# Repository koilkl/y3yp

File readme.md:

# 🥾 Next-Generation Ankle Rehabilitation System (Actuation Belt Trainer)

Welcome to the official repository for the **Next-Generation Ankle Rehabilitation System**, a biomechanically engineered solution designed to build structural resilience and prevent trail-induced lower-limb injuries. 

## 👥 Meet the Team
**Hikingggggggg(HKUST 2026 ISDN3001&ISDN3002 Group 1)**
* Teammate:Kwok Tsz Yueng
  * Kwok Tsz Yueng(Tom)
  * Li,Kaile(Koil)
  * Lee Wang Ngai(Cyrus)
  * Yu Kin Shing(Ken)

We are a team of passionate engineers and biomechanics enthusiasts dedicated to bridging the gap between clinical rehabilitation and real-world outdoor sports readiness.

---

## 🏔️ Project Overview

### The Problem: The Hiking Injury Epidemic
With the massive global expansion of hiking participation, there has been a severe spike in trail-induced injuries. 
* **Acute Lateral Sprains** account for an overwhelming 85% of all acute trail traumas.
* In competitive downhill races, lower-limb injury rates spike dramatically to 49%.
* Hikers face a **"Deficit in Terrain Adaptability"**; modern flat surfaces fail to prepare the body for the eccentric braking and instantaneous balance reflexes required on unpredictable mountain terrains (like loose rock and scree).

When a sudden, forceful ankle inversion exceeds 25 degrees, it tears the Anterior Talofibular and Calcaneofibular ligaments. 

### The Solution: The Actuation Belt Trainer
Existing market solutions force a compromise: balance boards train reflexes but lack heavy external load, while clinical dynamometers are expensive and lack multi-axis functional movement. 

After multiple ideation phases (including dynamic treadmills and linear pedal trainers), we finalized the **Actuation Belt Trainer**. This active, stationary device isolates the protective reflex arc by applying changeable, programmable external loads to train specific muscle reaction times across 3 Degrees of Freedom (DOFs).

---

## ⚙️ System Architecture

Our system integrates responsive hardware with a closed-loop software control mechanism to ensure precise resistance and user safety.

### Control Loop Workflow
1. **Command Input:** Users input commands via a terminal to wirelessly control motor force and turning direction for specific muscle targeting.
2. **Processing & Communication:** A Microcontroller Unit (MCU) processes the command using a PID controller and sends signals via a CAN Module to 6 Motor Electronic Speed Controllers (ESCs).
3. **IMU Feedback:** An Inertial Measurement Unit (IMU) under the pedal continuously detects the XYZ angle of the pedal.
4. **Evaluation & Visual Feedback:** The MCU calculates the control error against the target origin angle. If the user successfully holds the pedal within a +/- 10-degree range against the motor resistance for 5 seconds, an LED indicator triggers to signal successful completion.

---

## 🛠️ Component Design

The mechanical structure relies on motor-driven belts and gears to safely and effectively stimulate the ankle:

* **Roll Mechanism (Inversion/Eversion):** Four M3508 motors utilize a 1:1 gear transmission to transfer torque to a pulley system. This produces tension along an elastic belt connected to the pedal, creating a twisting motion that the user must resist.
* **Pitch Mechanism (Dorsiflexion/Plantarflexion):** A motor and gear turn the entire middle module and the central pedal, supported by a large external bearing for smooth turning. A limited angle of gear teeth physically restricts motion to guarantee it remains within an acceptable, safe anatomical range.

---

## 🔬 Biomechanical Validation

The system targets the biological failure points of the ankle by isolating the primary protective muscles:
* **Fibularis (Peroneal) Group:** Primary evertors critical for resisting sudden inward ankle rolling (inversion) on shifting scree.
* **Tibialis Group:** Crucial for dorsiflexion, arch support, and absorbing repeated impact with controlled eccentric braking during steep descents.

By engineering a device that challenges the ankle with resisted eversion and perturbation, the system is theoretically proven to improve strength and balance deficits.

---

## 🚀 Future Roadmap

* **Weeks 1-3:** Develop a dedicated mobile app for user control, design a "hiking-like" training mode, and improve mechanism functionalities.
* **Weeks 4-6:** Design pedals to fit different foot sizes, replace electronics to minimize overall device size, and refine the product outfit.
* **Weeks 6-7:** Conduct extensive user testing, identify potential new user groups, and perform evaluations based on feedback.
* **Weeks 7-8:** Design new features and establish a future plan for product line depth to fit various target demographics.

---

## 💾 Cloning This Repository

The repo uses **git submodules** (firmware) and **Git LFS** (large media files):

```bash
# 1. Install Git LFS (once per machine)
#    macOS:      brew install git-lfs
#    Windows:    winget install Git.LFS
#    Ubuntu:     sudo apt install git-lfs
git lfs install

# 2. Clone with submodules
git clone --recursive https://github.com/koilkl/y3yp.git
```

* `git lfs install` sets up the LFS filters on your machine. Without it, LFS-tracked files (e.g. `*.mp4`) are checked out as small pointer files instead of the real content.
* Already cloned without LFS support? Run `git lfs install && git lfs pull` to download the tracked files.
* `--recursive` fetches the firmware submodules under `ELEC/`; alternatively run `git submodule update --init --recursive` inside an existing clone.

## 📂 Repository Structure

```
y3yp/
├── DOCUMENT/                 # Presentations & demo video
│   └── Version-1.0/
│       ├── Midterm Presentation.pptx
│       ├── Final Presentation.pdf
│       └── demo video.mp4
├── ELEC/                     # Electronics & firmware
│   ├── Version-1.0/
│   │   └── Year_3_first_prototype/   # submodule: STM32F103C6T6, CAN motors + IMU + PID
│   └── Component/
│       └── Incliometer/              # submodule: STM32F401RETx, Modbus-RTU inclinometer
├── MECH/                     # Mechanical design (CAD)
│   └── Version-1.0/
│       └── Gen1-belt.zip             # Belt-actuation assembly (STEP)
└── readme.md                 # This file
```

## 📁 Resources & Appendices

* **CAD Files & 3D Renders:** [`MECH/Version-1.0/Gen1-belt.zip`](MECH/Version-1.0/Gen1-belt.zip)
* **Source Code (First Prototype):** [`yuu033/Year_3_first_prototype`](https://github.com/yuu033/Year_3_first_prototype) (submodule at [`ELEC/Version-1.0/Year_3_first_prototype/`](ELEC/Version-1.0/))
* **Source Code (Inclinometer Component):** [`koilkl/Incliometer`](https://github.com/koilkl/Incliometer) (submodule at [`ELEC/Component/Incliometer/`](ELEC/Component/))
* **Presentations:** [`DOCUMENT/Version-1.0/`](DOCUMENT/Version-1.0/README.md)
* **Prototype Demo Video:** [`DOCUMENT/Version-1.0/demo video.mp4`](DOCUMENT/Version-1.0/demo%20video.mp4)

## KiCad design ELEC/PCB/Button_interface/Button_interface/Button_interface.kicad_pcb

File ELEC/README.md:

# ⚡ ELEC — Electronics & Firmware

All electronics and embedded firmware for the **Actuation Belt Trainer**.

> The two firmware projects are **git submodules** pointing at their own repositories. Clone this repo with:
> ```bash
> git clone --recursive https://github.com/koilkl/y3yp.git
> ```
> If you already cloned without `--recursive`, run `git submodule update --init --recursive`.

## Layout

| Path | Description |
|------|-------------|
| [`Version-1.0/Year_3_first_prototype`](https://github.com/yuu033/Year_3_first_prototype) | Full first-prototype firmware (STM32F103C6T6): CAN motor control (C620 ESCs), IMU feedback (BMI270 + Modbus IMU), PID control loop |
| [`Component/Incliometer`](https://github.com/koilkl/Incliometer) | Standalone inclinometer data-acquisition project (STM32F401RETx, Modbus-RTU) used to validate pedal angle sensing |

## System Context

Both projects are STM32CubeMX-generated HAL projects built with CMake (`arm-none-eabi` GCC + Ninja). Together they implement the control loop described in the main [README](../readme.md): the MCU reads the pedal angle from an IMU, runs a PID controller, and drives the M3508/C620 motors over CAN to apply programmable resistance.

## Related

- Mechanical design: [`../MECH/`](../MECH/README.md)
- Presentations & demo: [`../DOCUMENT/`](../DOCUMENT/README.md)

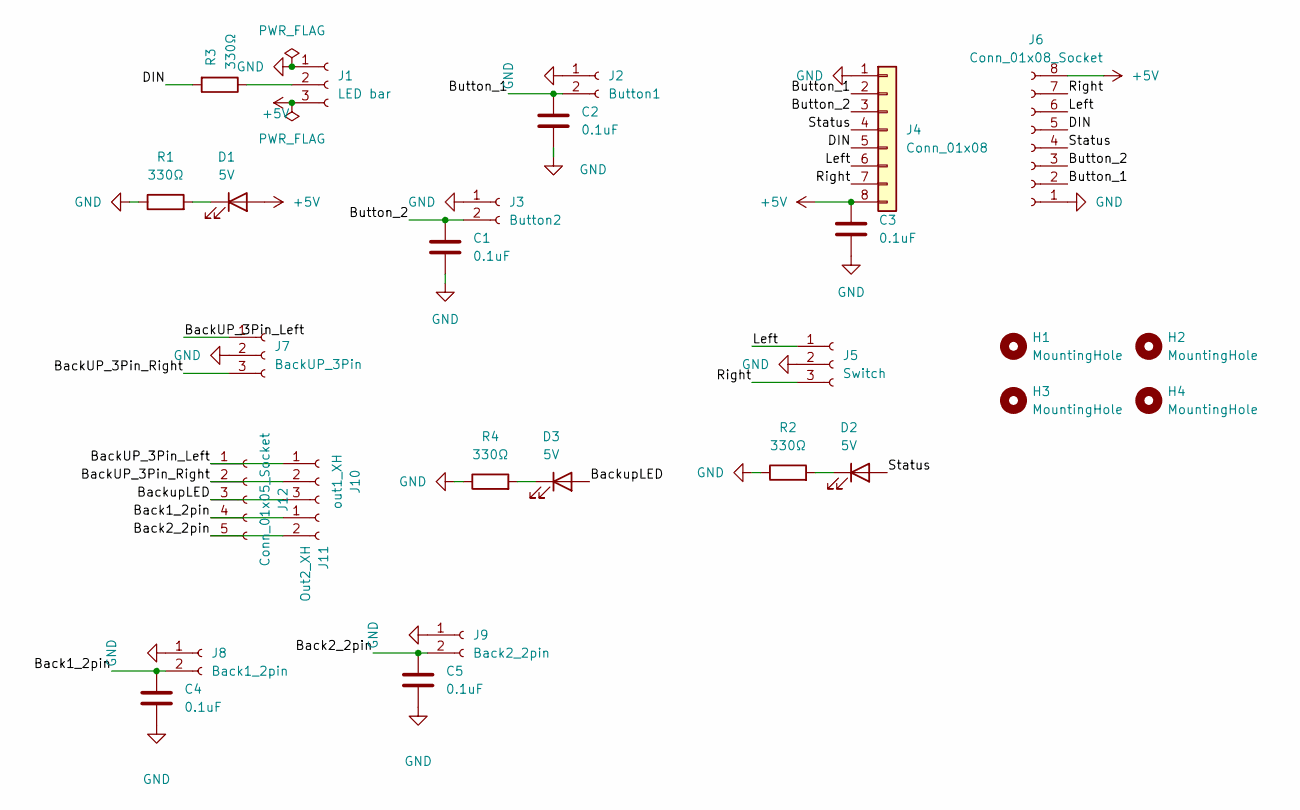
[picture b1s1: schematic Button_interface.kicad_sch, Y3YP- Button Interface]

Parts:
C1, C2, C3, C4, C5: 0.1uF; C_0805_2012Metric
D1, D2, D3: 5V; LED_D5.0mm
H1, H2, H3, H4: MountingHole; MountingHole_4.3mm_M4_DIN965_Pad
J1: LED bar; JST_XH_B3B-XH-A_1x03_P2.50mm_Vertical
J2: Button1; JST_XH_B2B-XH-A_1x02_P2.50mm_Vertical
J3: Button2; JST_XH_B2B-XH-A_1x02_P2.50mm_Vertical
J4: Conn_01x08; JST_XH_B8B-XH-A_1x08_P2.50mm_Vertical
J5: Switch; JST_XH_B3B-XH-A_1x03_P2.50mm_Vertical
J6: Conn_01x08_Socket; PinSocket_1x08_P2.54mm_Vertical
J7: BackUP_3Pin; JST_XH_B3B-XH-A_1x03_P2.50mm_Vertical
J8: Back1_2pin; JST_XH_B2B-XH-A_1x02_P2.50mm_Vertical
J9: Back2_2pin; JST_XH_B2B-XH-A_1x02_P2.50mm_Vertical
J10: out1_XH; JST_XH_B3B-XH-A_1x03_P2.50mm_Vertical
J11: Out2_XH; JST_XH_B2B-XH-A_1x02_P2.50mm_Vertical
J12: Conn_01x05_Socket; PinSocket_1x05_P2.54mm_Vertical
R1, R2, R3, R4: 330Ω; R_0805_2012Metric

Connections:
+5V: C3.1, D1.2 (A), J1.3, J4.8, J6.8
/Back1_2pin: C4.1, J8.2, J11.1, J12.4
/Back2_2pin: C5.1, J9.2, J11.2, J12.5
/BackUP_3Pin_Left: J7.1, J10.1, J12.1
/BackUP_3Pin_Right: J7.3, J10.2, J12.2
/BackupLED: D3.2 (A), J10.3, J12.3
/Button_1: C2.1, J2.2, J4.2, J6.2
/Button_2: C1.1, J3.2, J4.3, J6.3
/DIN: J4.5, J6.5, R3.2
/Left: J4.6, J5.1, J6.6
/Right: J4.7, J5.3, J6.7
/Status: D2.2 (A), J4.4, J6.4
GND: C1.2, C2.2, C3.2, C4.2, C5.2, J1.1, J2.1, J3.1, J4.1, J5.2, J6.1, J7.2, J8.1, J9.1, R1.1, R2.1, R4.1
unnamed: D1.1 (K), R1.2
unnamed: D2.1 (K), R2.2
unnamed: D3.1 (K), R4.2
unnamed: J1.2, R3.1

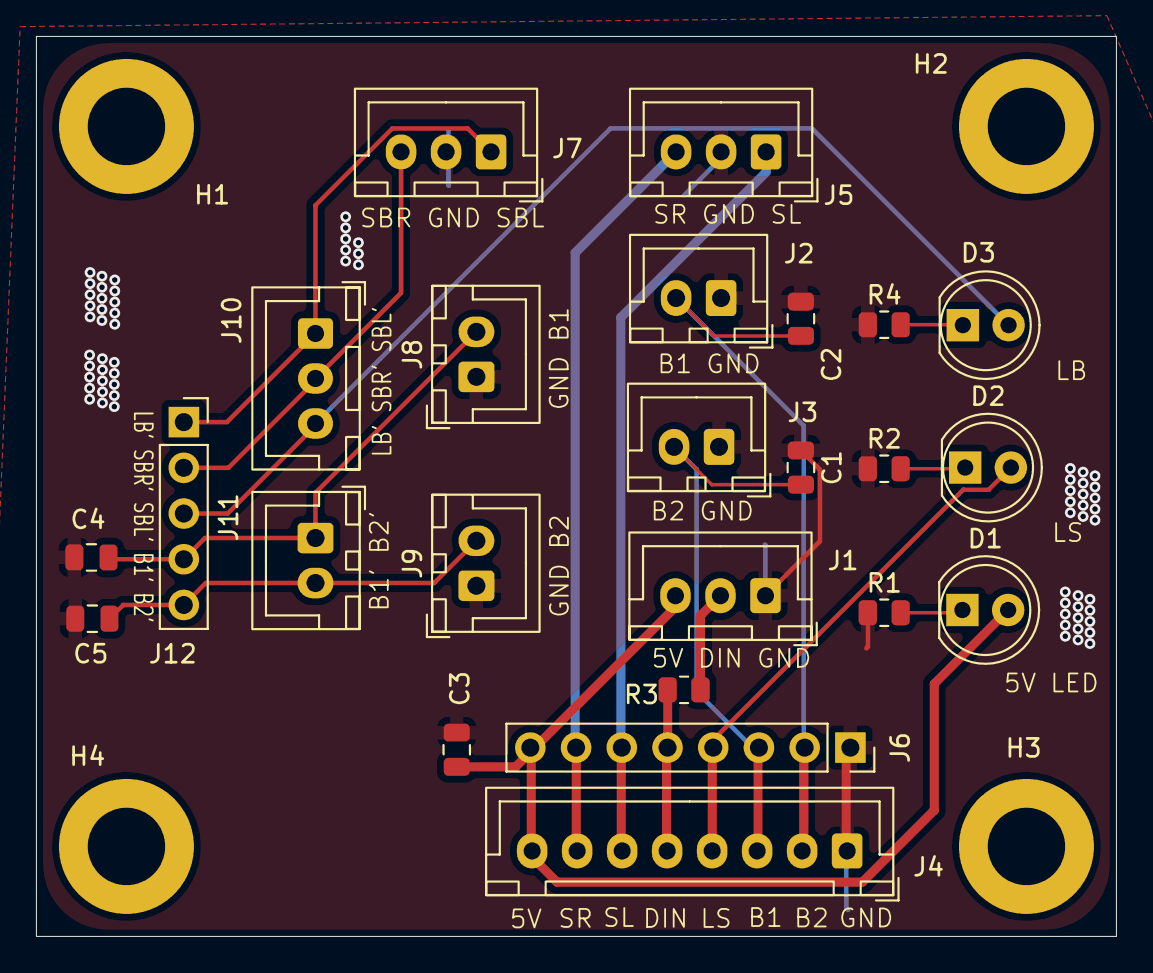
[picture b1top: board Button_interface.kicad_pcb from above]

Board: 2 copper layers, 60.0 x 50.0 mm, 28 parts (0 on the bottom side), 17 nets.

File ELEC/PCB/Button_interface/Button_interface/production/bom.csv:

Designator,Footprint,Quantity,Value,LCSC Part #
"C1, C2, C3, C4, C5",0805,5,0.1uF,
"D1, D2, D3",LED_D5.0mm,3,5V,
J1,JST_XH_B3B-XH-A_1x03_P2.50mm_Vertical,1,LED bar,
J10,JST_XH_B3B-XH-A_1x03_P2.50mm_Vertical,1,out1_XH,
J11,JST_XH_B2B-XH-A_1x02_P2.50mm_Vertical,1,Out2_XH,
J12,PinSocket_1x05_P2.54mm_Vertical,1,Conn_01x05_Socket,
J2,JST_XH_B2B-XH-A_1x02_P2.50mm_Vertical,1,Button1,
J3,JST_XH_B2B-XH-A_1x02_P2.50mm_Vertical,1,Button2,
J4,JST_XH_B8B-XH-A_1x08_P2.50mm_Vertical,1,Conn_01x08,
J5,JST_XH_B3B-XH-A_1x03_P2.50mm_Vertical,1,Switch,
J6,PinSocket_1x08_P2.54mm_Vertical,1,Conn_01x08_Socket,
J7,JST_XH_B3B-XH-A_1x03_P2.50mm_Vertical,1,BackUP_3Pin,
J8,JST_XH_B2B-XH-A_1x02_P2.50mm_Vertical,1,Back1_2pin,
J9,JST_XH_B2B-XH-A_1x02_P2.50mm_Vertical,1,Back2_2pin,
"R1, R2, R3, R4",0805,4,330Ω,
